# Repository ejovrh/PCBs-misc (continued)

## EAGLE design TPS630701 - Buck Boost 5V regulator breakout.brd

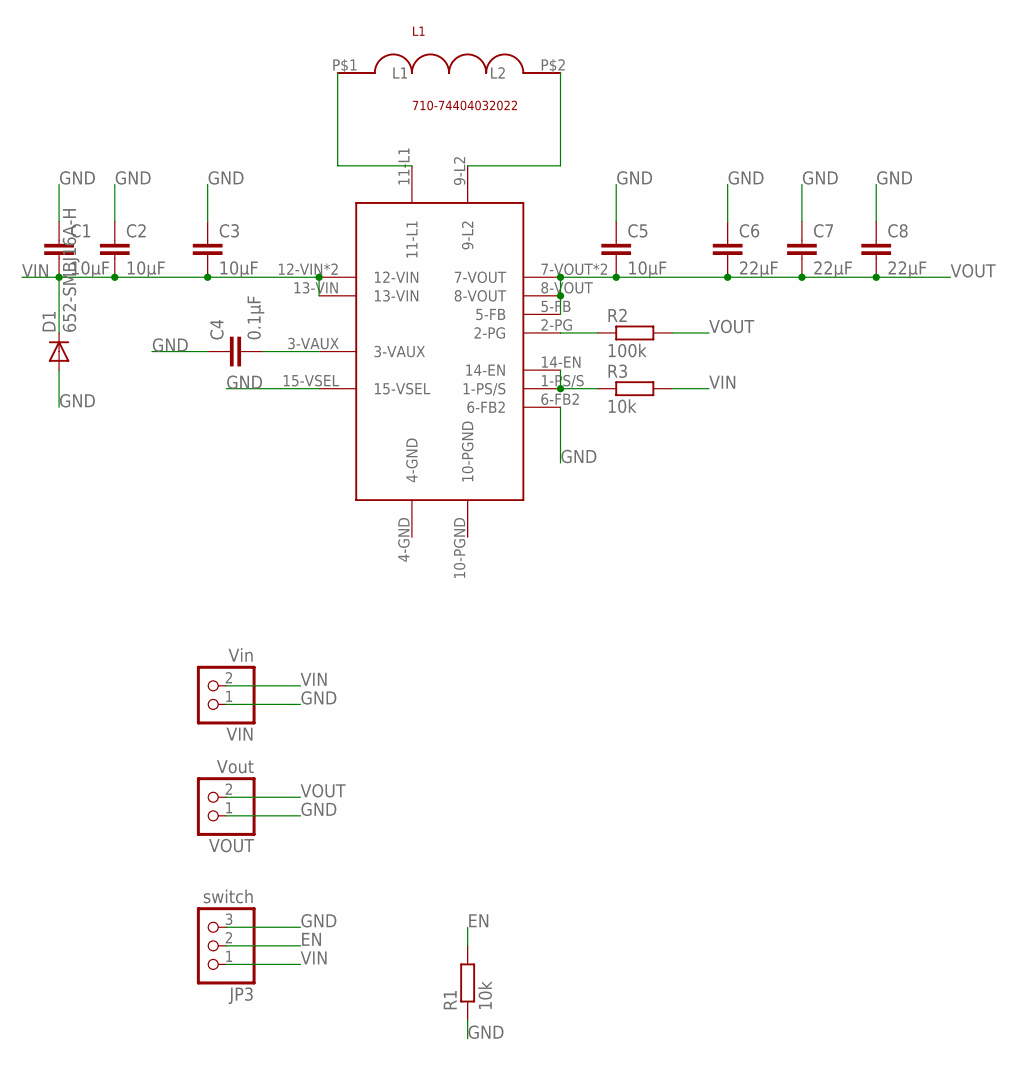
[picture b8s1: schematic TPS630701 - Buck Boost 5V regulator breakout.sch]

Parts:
C1, C2: 10μF; C0805
C3, C5: 10μF; C0603
C4: 0.1μF; C0805
C6, C7, C8: 22μF; C0805
D1: 652-SMBJ16A-H; DO214AA
IC1: TPS630701RNMT; VQFN
JP3: switch; 1X03
L1: 710-74404032022; FFF
R1, R3: 10k; R0805
R2: 100k; R0805
VIN: Vin; 1X02
VOUT: Vout; 1X02

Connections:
EN: JP3.2, R1.2
GND: C1.1, C2.1, C3.1, C4.1, C5.1, C6.1, C7.1, C8.1, D1.A, IC1.6-FB2, IC1.15-VSEL, JP3.3, R1.1, VIN.1, VOUT.1
L1: IC1.11-L1, L1.P$1 (L1)
L2: IC1.9-L2, L1.P$2 (L2)
unnamed: IC1.1-PS/S, IC1.14-EN, R3.1
PG: IC1.2-PG, R2.1
VAUX: C4.2, IC1.3-VAUX
VIN: C1.2, C2.2, C3.2, D1.C, IC1.12-VIN, IC1.13-VIN, IC1.VIN (12-VIN), JP3.1, R3.2, VIN.2
VOUT: C5.2, C6.2, C7.2, C8.2, IC1.5-FB, IC1.7-VOUT, IC1.8-VOUT, IC1.VOUT (7-VOUT), R2.2, VOUT.2

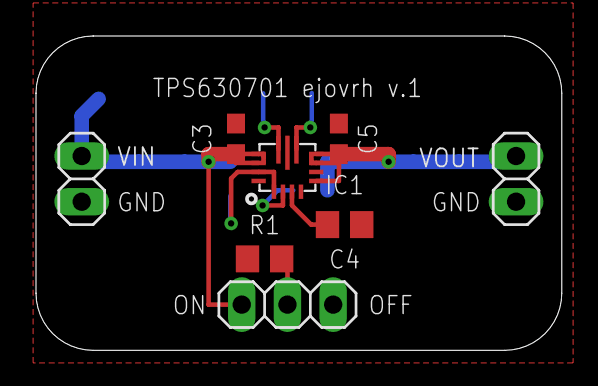
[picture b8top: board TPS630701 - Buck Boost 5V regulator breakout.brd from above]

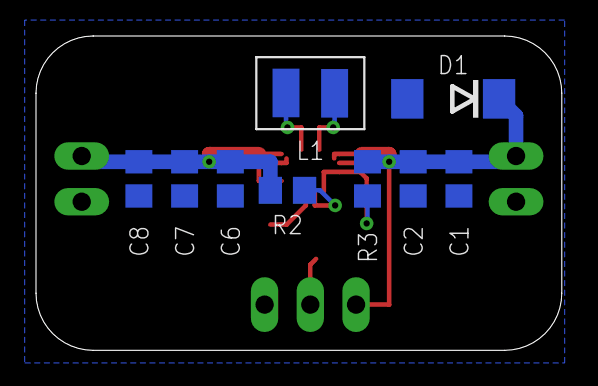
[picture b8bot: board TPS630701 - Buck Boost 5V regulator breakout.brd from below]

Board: 2 copper layers, 29.2 x 17.5 mm, 17 parts (9 on the bottom side), 9 nets.

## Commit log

2017-10-01 - Nikon D700 (and similar) "10-pin connector" to "something accessible with probes (aka. 2.54mm header strip)"
2017-10-01 - TPS63031 voltage regulator: dc-dc from 0-7 to 3.3V with ~2A load capability
2017-10-01 - OriginGPS ORG1510-MK4 breakout board with a few passives and zener-overvoltage protetion
2017-10-01 - minor corrections on GPS board (tplace/bplace stuff)
2017-10-07 - corrected the "ejovrh"
2017-12-17 - corrected routing neat the PCB edge
2017-12-17 - final gerber commit before production
2017-12-18 - redo of gerbers with new cam job
2017-12-22 - corrected 10-pin library (diameter of pins) and updated breakout board
2017-12-24 - added eagle.epf
2017-12-24 - updated TPS63031 device name & redo of gerbers - added BOM
2017-12-24 - added BOM for gps brekaout
2018-01-04 - added + and - markings on in and out - improved ground traces
2018-01-05 - adjusted board dimensions & updated gerbers
2018-01-05 - created LTC4425 breakout board
2018-01-05 - added ground vias around board edges
2018-02-11 - LM74670 ideal diode breakout board
2018-02-11 - created gerbers for LM74670 ideal diode breakout board
2018-02-11 - created a few eagle design block
2018-02-11 - added diode rectifier breakout
2018-02-11 - corrected diode rectifier board layout & regenerated gerbers
2018-02-11 - converted element to design block
2018-02-11 - updated LTC4425 breakout: replaced the supercap, modified tplace strings
2018-02-11 - added dimensions
2018-02-17 - removed supercap from board and made it generic - updated gerbers and design block
2018-04-25 - finalized LTC4425 breakout.brd, written BOM and created gerbers
2018-04-25 - finalized LM74670 ideal diode breakout.brd, written BOM and created gerbers
2018-04-26 - finalized diode recfifier.brd, written BOM and created gerbers
2018-04-26 - finalized TPS630701 - Buck Boost 5V regulator breakout.brd, written BOM and created gerbers
2018-04-26 - renamed BOM files
2018-05-01 - updated LTC4425 breakout with 0402 SMD passives, updated BOM and gerbers
2018-05-01 - corrected passives form factor in BOM
2018-05-02 - created MCP2561 & MCP2515 CAN breakout borard, BOM, gerbers, ERC & DRC check out ok
2018-05-03 - corrected one drill diameter & recreated gerbers (were missing the dimension layer)
2018-05-03 - recreated gerbers with better layer names
2018-05-03 - recreated gerbers with better layer names & corrected mission dimension layer
2018-05-04 - corrected gerber file format to rs-274x
2018-05-12 - made ground plane for diode-common thicker
2018-05-12 - ideal diode breakout: minor corrections in tplace, thickened ground planes
2018-05-12 - ideal diode breakout: saved previous changes as design block
2018-05-27 - added MAX6818-debounced mini keyboard
2018-05-27 - created gerbers for joystick-tact breakout; DRC & ERC are error-free
2018-05-27 - created LP38693 5V LDO breakout board brd, sch and gerbers; RDC & ERC are error free
2018-05-30 - added pullup to reset pin on MCP2515-2561 CAN brekaout.brd
2018-06-10 dummy test code for an arduino uno and the breakout board
2018-06-10 - modified ignorelist
2018-06-14 - blink test via CAN message
2018-06-14 - copied most recent mj808.h
2018-06-16 - imported mj808.h and updated main() whit define'd values - introduced test for CMND_DEVICE - DEV_LIGHT - front light (on/off/fade commands with single light) - introduced test for CMND_UTIL_LED
2018-06-16 - added 4 remaining buttons for some UI - added tests for high beam and brake light
2018-06-21 - added GREEN & RED define of hex value for commands - added mj8x8 class definition
2018-06-29 - introduced object oriented representation of the two lights (it's ugly)
2018-07-03 - reorganized SID byte structure a bit (swapped places of sender dev. id and rcpt. dev. class) for easier coding
2018-07-10 - updated mj8x8.h to match other repos
2019-01-02 - recreated epf - eagle project identifier file
2019-03-26 - created LDK320ADU50R 5V0 LDO breakout.brd & design block
2019-04-02 - finished LDK320ADU50R 5V0 LDO breakout, created BOM, ran DRC & ERC
2019-04-02 - updated LP38693 5V LDO breakout, ran ERC&DRC, created BOM and dbl
2021-04-05 - added adapter PCB for Rigol DL3021 Binding Post to Banana Jack
2021-04-06 - added current sense resistor breakout board for measuring currents with an oscilloscope
2022-11-21 added TAG connect eagle library
2023-03-15 updated TAG connect footprints
